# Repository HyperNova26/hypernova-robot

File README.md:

<div align="center">
  
  <p><strong>HyperNova 로봇 프로젝트</strong></p>
</div>

## 프로젝트

HyperNova는 스스로 움직이는 로봇을 직접 설계해서 만드는 팀 프로젝트입니다!

## 다루는 영역

- 이동과 기체 제어
- 주변 인지와 위치 추정
- 자율 임무 수행과 상태 보고
- 시험, 관제, 시스템 레벨 통합

## 저장소 구조

| 경로 | 역할 |
| --- | --- |
| [`docs/`](./docs/) | 프로젝트 범위, 아키텍처, 개발·운용 지침, 결정 기록 |
| [`description/`](./description/) | URDF·Xacro, frame·joint와 실행에 필요한 mesh |
| [`firmware/`](./firmware/) | 보드별 펌웨어, 플래시 및 진단 도구 |
| [`ros_pkgs/`](./ros_pkgs/) | 기능별 ROS 2 package와 관제 애플리케이션 |
| [`sim_scenes/`](./sim_scenes/) | 시뮬레이션 환경과 검증 시나리오 |
| [`policies/`](./policies/) | 학습 기반 policy의 학습·평가·export 코드와 설정 |
| [`tools/`](./tools/) | 개발·검증·변환 도구 |

## 시작하기

1. [프로젝트 범위](./docs/project-scope.md) — 무엇이 정해졌고 무엇이 아직 비어 있는지
2. [`CONTRIBUTING.md`](./CONTRIBUTING.md) — Issue에서 시작해 branch, Pull Request로 가는 흐름
3. [저장소 정책](./docs/development/repository-policy.md) — 큰 파일이나 센서 데이터를 올리기 전에
4. [안전 지침](./docs/operations/safety.md) — 실물에 전원을 넣기 전에

## 문서

- [문서 색인](./docs/README.md)
- [시뮬레이터 장면 변환 안내](./sim_scenes/README.md) — 전체 점군 변환과 미완성 segmentation의 현재 범위
- [ADR-0001: 단일 저장소로 시작](./docs/decisions/0001-monorepo-first.md)

2026-11-26 기준, `tools/`와 `tests/`의 코드는 처음 저장소에 들어온 날짜를 붙인 `MMDD_이름`으로 부릅니다. 맵 도구 목록과 PAIR360 지도 v1·v2·v3의 대응은 [도구 안내](./tools/README.md)에 있습니다.

## 라이선스

산출물 종류에 따라 라이선스가 다릅니다.

- 소프트웨어·펌웨어·시뮬레이션·학습·도구: Apache-2.0
- 기구·전자 설계와 그 파생 형상·제조 산출물: CERN-OHL-S-2.0
- 문서: CC BY 4.0
- HYPERNOVA 이름·로고·배너: 라이선스 대상 아님

적용 범위와 원문은 [`LICENSE.md`](./LICENSE.md)에 있습니다.

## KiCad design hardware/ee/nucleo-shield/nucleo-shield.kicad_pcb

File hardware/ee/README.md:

<!-- SPDX-License-Identifier: CC-BY-4.0 -->

# HyperNova Nucleo 캐리어 P2.3

2026-11-28 시제품 발주 전 설계 검토본입니다. NUCLEO-G474RE가 다리별 RS-485 버스 4개로 모터 12대를 제어합니다. KiCad 10.0.6에서 [전용 라이브러리를 포함한 프로젝트](nucleo-shield/nucleo-shield.kicad_pro)를 엽니다.

J17에는 부하가 걸린 상태에서 5.15–5.25 V인 안정화 전원을 연결합니다. F1과 LTC4364-2 공통 보호단을 지나 두 갈래로 나뉩니다. 한쪽은 J24에서 6 V로 승압한 뒤 U6·U14를 통해 Nucleo CN7-6과 J14-6에 전원을 공급합니다. 다른 쪽은 8핀 J23의 TI 벅을 통해 J19–J22의 RS-485 모듈 네 개에 전용 3.3 V를 공급합니다. Nucleo와 모듈은 GND를 공유합니다. 양쪽 전원이 유효하고 펌웨어의 공통 허용 신호와 채널별 DE가 켜져야 송신할 수 있습니다. J7–J11의 센서 전원은 Nucleo 3.3 V입니다.

J14의 CAN FD 모듈을 통해 Jetson에 통신하고, 외장 션트와 J13의 INA228으로 얻은 측정값을 Jetson의 배터리 잔량 표시에 사용합니다. J15는 라이다 동기 입력이고 J16은 필수 경고음용 피에조입니다. 모터 전력·퓨즈·비상 차단은 외부 하네스에 두며, PA11의 J18은 기본 미실장입니다.

| 검토 자료 | 확인할 내용 |
| --- | --- |
| [전원 계산서와 시제품 시험표](nucleo-shield/power-validation.md) · [계산 재현 스크립트](nucleo-shield/check-power-margins.py) | CN7·원격 RS 전압 여유, 기동·저전압 감시, 핫플러그 보호 범위와 시험 조건 |
| [KiCad 및 제조 파일 검증](nucleo-shield/verification.md) | 검사 환경과 결과, 동박 사양, Gerber·드릴 검토본 |
| [캐리어 BOM](nucleo-shield/carrier-bom.csv) · [구매 BOM](nucleo-shield/modules-and-mates.csv) | 실장·DNP, 완성 모듈, 커넥터와 하네스 부품의 구매 조건 |
| [조립 안내](nucleo-shield/assembly.md) · [하네스 제작표](nucleo-shield/harnesses.md) | 조립면, 핀 순서, 선경·길이, 종단·센스선 보호 |

발주 결정은 설계팀 검토 후 진행합니다. 시제품 전원과 통신의 실측 결과를 양산 판단에 사용합니다. 전자 설계에는 CERN-OHL-S-2.0, 문서에는 CC BY 4.0을 적용합니다. [저장소 라이선스](../../LICENSE.md)

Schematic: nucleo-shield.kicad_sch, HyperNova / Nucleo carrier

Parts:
C1: 4.7u; C_Disc_D5.0mm_W2.5mm_P2.50mm
C2, C5, C6, C7, C8, C15, C16, C17, C18, C19, C21: 100n; C_Disc_D5.0mm_W2.5mm_P2.50mm
C3, C14, C20: 22u / 25V X7R; C_Rect_L7.5mm_W6.5mm_P5.00mm
C4: 100n; C_Disc_D5.0mm_W2.5mm_P2.50mm; not fitted
C9: 22u / 50V NP; C_Radial_D10.0mm_H12.5mm_P5.00mm
C10: 10n; C_Disc_D5.0mm_W2.5mm_P2.50mm
C11: 12n C0G; C_Disc_D5.0mm_W2.5mm_P2.50mm
C12, C13, C25: 100n / 50V; C_Disc_D5.0mm_W2.5mm_P2.50mm
C22: 68n 5% / 50V; C_Rect_L7.2mm_W3.5mm_P5.00mm
C23: 47n 5% / 50V; C_Rect_L7.2mm_W3.5mm_P5.00mm
C24: 680u / 25V low ESR; CP_Radial_D10.0mm_P5.00mm
C26: 10u / 25V X7R; C_Rect_L7.5mm_W6.5mm_P5.00mm
D1: CAN; LED_D3.0mm
D2: RUN; LED_D3.0mm
D3: FAULT; LED_D3.0mm
D4, D5: BAT43; D_DO-35_SOD27_P2.54mm_Vertical_CathodeUp
D6, D7, D8: BAT43; D_DO-35_SOD27_P2.54mm_Vertical_CathodeUp; not fitted
D9: P6KE30CA; D_DO-15_P10.16mm_Horizontal
D10: SB1100-T; D_DO-41_SOD81_P7.62mm_Horizontal
D11: LM4040AIZ-2.5; TO-92_Inline
D12: 1N4750A 27V; D_DO-41_SOD81_P7.62mm_Horizontal
D13: BAT85; D_DO-35_SOD27_P2.54mm_Vertical_CathodeUp
D14, D15: BZX55C12; D_DO-35_SOD27_P2.54mm_Vertical_CathodeUp
D16: 5KP6.5A; Littelfuse_5KP_P20mm
D17: LT1634CCZ-2.5; TO-92_Inline
F1: 0251002.MXL; R_Axial_DIN0207_L6.3mm_D2.5mm_P10.16mm_Horizontal
J1: CN7 / MORPHO; Morpho_Socket_2x19_P2.54mm_Top_Mating
J2: CN10 / MORPHO; Morpho_Socket_2x19_P2.54mm_Top_Mating
J3: LEG1 RS485; JST_XH_S3B-XH-A_1x03_P2.50mm_Horizontal
J4: LEG2 RS485; JST_XH_S3B-XH-A_1x03_P2.50mm_Horizontal
J5: LEG3 RS485; JST_XH_S3B-XH-A_1x03_P2.50mm_Horizontal
J6: LEG4 RS485; JST_XH_S3B-XH-A_1x03_P2.50mm_Horizontal
J7: TOF1; JST_PH_S5B-PH-K_1x05_P2.00mm_Horizontal
J8: TOF2; JST_PH_S5B-PH-K_1x05_P2.00mm_Horizontal
J9: TOF3; JST_PH_S5B-PH-K_1x05_P2.00mm_Horizontal
J10: TOF4; JST_PH_S5B-PH-K_1x05_P2.00mm_Horizontal
J11: BMI088; PinHeader_1x09_P2.54mm_Vertical
J13: INA228 LOGIC; JST_PH_B4B-PH-K_1x04_P2.00mm_Vertical
J14: CAN FD 3 CLICK; JST_XH_B6B-XH-A_1x06_P2.50mm_Vertical
J15: JST-GH SYNC; JST_GH_SM04B-GHS-TB_1x04-1MP_P1.25mm_Horizontal
J16: BUZZER 3V3; JST_PH_B2B-PH-K_1x02_P2.00mm_Vertical
J17: REGULATED 5V; JST_XH_B2B-XH-A_1x02_P2.50mm_Vertical
J18: DRY NC CONTACT; JST_PH_B3B-PH-K_1x03_P2.00mm_Vertical; not fitted
J19, J20, J21, J22: TI THVD1424EVM; JST_XH_B7B-XH-A_1x07_P2.50mm_Vertical
J23: TPSM365R6V3EVM; JST_XH_B8B-XH-A_1x08_P2.50mm_Vertical
J24: POLOLU U3V16F6 #4942; Pololu_4942_VerticalSocket
Q1, Q2: 2N3904; TO-92_Inline
Q3, Q4: IRLZ44NPBF; TO-220-3_Vertical
R1, R7, R8, R19, R66: 10k; R_Axial_DIN0207_L6.3mm_D2.5mm_P2.54mm_Vertical
R6: 4.7k; R_Axial_DIN0207_L6.3mm_D2.5mm_P2.54mm_Vertical
R9, R10, R11, R12: 4.7k; R_Axial_DIN0207_L6.3mm_D2.5mm_P2.54mm_Vertical; not fitted
R13: 1.5k; R_Axial_DIN0207_L6.3mm_D2.5mm_P2.54mm_Vertical
R14, R15, R16, R17, R18: 1k; R_Axial_DIN0207_L6.3mm_D2.5mm_P2.54mm_Vertical
R28: 1k; R_Axial_DIN0207_L6.3mm_D2.5mm_P2.54mm_Vertical; not fitted
R29: 10k; R_Axial_DIN0207_L6.3mm_D2.5mm_P2.54mm_Vertical; not fitted
R30, R31, R32, R33: 120R; R_Axial_DIN0207_L6.3mm_D2.5mm_P2.54mm_Vertical; not fitted
R35: 93.1k 0.1%; R_Axial_DIN0207_L6.3mm_D2.5mm_P2.54mm_Vertical
R36: 3.9k; R_Axial_DIN0207_L6.3mm_D2.5mm_P2.54mm_Vertical
R37: 1.82k 0.1%; R_Axial_DIN0207_L6.3mm_D2.5mm_P2.54mm_Vertical
R38: 976R 1%; R_Axial_DIN0207_L6.3mm_D2.5mm_P2.54mm_Vertical
R39: 100R; R_Axial_DIN0207_L6.3mm_D2.5mm_P2.54mm_Vertical
R40: 3.30k; R_Axial_DIN0207_L6.3mm_D2.5mm_P2.54mm_Vertical
R41, R42: 10.0k 0.1%; R_Axial_DIN0207_L6.3mm_D2.5mm_P2.54mm_Vertical
R43: 33.2k 0.1%; R_Axial_DIN0207_L6.3mm_D2.5mm_P2.54mm_Vertical
R44, R46, R62: 10k 0.1%; R_Axial_DIN0207_L6.3mm_D2.5mm_P2.54mm_Vertical
R45: 19.1k 0.1%; R_Axial_DIN0207_L6.3mm_D2.5mm_P2.54mm_Vertical
R47: 22k; R_Axial_DIN0207_L6.3mm_D2.5mm_P2.54mm_Vertical
R48: 15k; R_Axial_DIN0207_L6.3mm_D2.5mm_P2.54mm_Vertical
R49, R50, R51, R52, R53, R54, R55, R56: 390R; R_Axial_DIN0207_L6.3mm_D2.5mm_P2.54mm_Vertical; not fitted
R57: 59.7k 0.1%; R_Axial_DIN0207_L6.3mm_D2.5mm_P2.54mm_Vertical
R61: 51.1k 0.1%; R_Axial_DIN0207_L6.3mm_D2.5mm_P2.54mm_Vertical
R63: 576R 0.1%; R_Axial_DIN0207_L6.3mm_D2.5mm_P2.54mm_Vertical
R64: 2.49k 0.1%; R_Axial_DIN0207_L6.3mm_D2.5mm_P2.54mm_Vertical
R65: 1.50k 1%; R_Axial_DIN0207_L6.3mm_D2.5mm_P2.54mm_Vertical
R67: 180R; R_Axial_DIN0207_L6.3mm_D2.5mm_P2.54mm_Vertical
R68: 27m / 5W / 10%; KOA_BPR58_P9.0mm
R69, R71: 3.48k 0.1%; R_Axial_DIN0207_L6.3mm_D2.5mm_P2.54mm_Vertical
R70, R72: 1.00k 0.1%; R_Axial_DIN0207_L6.3mm_D2.5mm_P2.54mm_Vertical
R73: 10R; R_Axial_DIN0207_L6.3mm_D2.5mm_P2.54mm_Vertical
R74: 0.68R / 3W pulse; Vishay_AC03_P17.78mm
R75: 0.33R / 5W pulse; Vishay_AC05_P25.4mm
RN1, RN3: 4x 4.7k; R_Array_SIP5
RN2, RN4, RN5: 4x 10k; R_Array_SIP5
RN6, RN7: 4x 47k; R_Array_SIP5
TP1: E5V_PROTECTED; TestPoint_THTPad_D1.5mm_Drill0.7mm
TP2: +3V3; TestPoint_THTPad_D1.5mm_Drill0.7mm
TP3: GND; TestPoint_THTPad_D1.5mm_Drill0.7mm
U1: 74HC08; DIP-14_W7.62mm
U6: LT3086ET7#PBF; TO-220-7_P2.54x3.7mm_StaggerOdd_Lead3.8mm_Vertical
U7: LM393AP; DIP-8_W7.62mm
U9, U10, U11: SN74AHC126N; DIP-14_W7.62mm
U13: LTC2909-3.3 / PA0089; ProtoAdvantage_PA0089_DIP8
U14: TPS2553 / PA0085; ProtoAdvantage_PA0085_DIP6
U15: SN74HC14N; DIP-14_W7.62mm
U16: LTC4364-2 / PA0005; ProtoAdvantage_PA0005_DIP16

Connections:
/+3V3: C1.1, C2.1, C17.1, D4.1 (K), D6.1 (K), D7.1 (K), J1.16, J7.1, J8.1, J9.1, J10.1, J11.1, J13.1, J14.1, J16.1, R6.1, R7.1, R8.1, R9.1, R10.1, R11.1, R12.1, R13.1, R29.1, R61.1, RN2.1 (common), TP2.1 (1_1), U1.14 (VCC), U11.14 (VCC)
/+3V3_RS485: C5.1, C6.1, C7.1, C8.1, C15.1, C16.1, C18.1, C21.1, D17.2 (K), J19.1, J20.1, J21.1, J22.1, J23.5, R49.2, R51.2, R53.2, R55.2, R65.1, RN3.1 (common), RN5.1 (common), U9.14 (VCC), U10.14 (VCC), U13.6 (VCC), U13.8 (SEL), U15.14 (VCC)
/BOOST_6V: C13.1, C26.1, J24.3, U6.5 (IN)
/BUCK_EN: D13.2 (A), J23.2
/BUZZER_BASE: Q1.2 (B), R18.2, R19.1
/BUZZER_PWM: J2.24, R18.1
/BUZZER_SINK: D6.2 (A), J16.2, Q1.3 (C)
/CAN_RX: J2.16, J14.4
/CAN_STB: J2.26, J14.5, R6.2
/CAN_TX: J2.30, J14.3
/E5V_ILIM: R57.1, U14.5 (ILIM)
/E5V_PROTECTED: C20.1, J1.6, J14.6, TP1.1 (1_1), U14.6 (OUT)
/E5V_REG: C3.1, C10.1, C14.1, C19.1, R35.1, R36.1, U6.3 (OUT), U14.1 (IN), U14.3 (EN)
/ESTOP_AUX_RAW: J18.1, R28.2
/ESTOP_STATUS: C4.1, D7.2 (A), D8.1 (K), J2.14, R28.1, R29.2
/EXT_5V_FUSED: C9.1, C25.1, D9.1 (A1), D10.2 (A), F1.1, R71.1, R75.1, U16.8 (VCC)
/EXT_5V_IN: F1.2, J17.1
/GND: C1.2, C2.2, C3.2, C4.2, C5.2, C6.2, C7.2, C8.2, C9.2, C11.2, C12.2, C13.2, C14.2, C15.2, C16.2, C17.2, C18.2, C19.2, C20.2, C21.2, C22.2, C23.2, C24.2, C25.2, C26.2, D1.1 (K), D2.1 (K), D3.1 (K), D5.2 (A), D8.2 (A), D9.2 (A2), D11.3 (A), D12.2 (A), D16.2 (A), J1.8, J1.19, J1.20, J1.22, J2.9, J2.20, J3.3, J4.3, J5.3, J6.3, J7.2, J8.2, J9.2, J10.2, J11.2, J13.2, J14.2, J15.2, J17.2, J18.3, J19.2, J20.2, J21.2, J22.2, J23.4, J23.6, J24.2, Q1.1 (E), R1.2, R19.2, R36.2, R37.2, R42.2, R44.2, R46.2, R48.2, R50.1, R52.1, R54.1, R56.1, R57.2, R62.2, R64.2, R66.2, R70.2, R72.2, RN1.1 (common), RN4.1 (common), RN6.1 (common), RN7.1 (common), TP3.1 (1_1), U1.7 (GND), U6.4 (GND), U7.4 (V-), U9.7 (GND), U10.7 (GND), U11.7 (GND), U13.4 (GND), U13.7 (TMR), U14.2 (GND), U15.5 (3A), U15.7 (GND), U15.9 (4A), U15.11 (5A), U15.13 (6A), U16.12 (GND)
/IMU_CSB1: J1.32, J11.6, R7.2
/IMU_CSB2: J1.34, J11.7, R8.2
/IMU_INT1: J1.35, J11.8
/IMU_INT3: J1.37, J11.9
/IMU_MISO: J2.13, J11.5
/IMU_MOSI: J2.15, J11.4
/IMU_SCK: J2.11, J11.3
/J17_AUX: C12.1, D12.1 (K), Q2.3 (C), R39.1, R40.1, R43.1, R45.1, U7.8 (V+)
/J17_COMP: C11.1, R38.2
/J17_DAMPED: Q3.2 (D), R75.2
/J17_DIODE: D10.1 (K), R39.2
/J17_GATE: D13.1 (K), Q2.2 (B), R47.2, U7.1, U7.7, U16.10 (UV)
/J17_HALF: R41.2, R42.1, U7.3 (+), U7.6 (-)
/J17_IMON: R37.1, R38.1, U6.1 (ILIM)
/J17_ISENSE: Q4.2 (D), R68.1, U16.2 (SENSE)
/J17_OV: R43.2, R44.1, U7.2 (-)
/J17_PROTECTED: C24.1, D16.1 (K), J24.1, R68.2, R69.1, R74.1, U16.1 (OUT)
/J17_REF: D11.2 (K), R40.2, R41.1, R47.1
/J17_SET: C10.2, R35.2, U6.2 (SET)
/J17_SHDN: Q2.1 (E), R48.1, U6.6 (SHDN)
/J17_UV: R45.2, R46.1, U7.5 (+)
/LED_CAN: J1.38, R15.1
/LED_FAULT: J2.33, R17.1
/LED_RUN: J1.36, R16.1
/LEG1_A: J3.1, J19.6, R30.2, R49.1
/LEG1_B: J3.2, J19.7, R30.1, R50.2
/LEG1_DE: J1.17, RN1.2 (R1), U1.1 (A)
/LEG1_DI: J19.4, RN5.2 (R1), U9.3 (1Y)
/LEG1_DRIVE: RN7.2 (R1), U1.3 (Y), U10.2 (1A)
/LEG1_RO: J19.3, RN3.2 (R1), U11.2 (1A)
/LEG1_RSE: J19.5, RN4.2 (R1), U10.3 (1Y)
/LEG1_RX: J1.2, RN2.2 (R1), U11.3 (1Y)
/LEG1_TX: J1.1, RN6.2 (R1), U9.2 (1A)
/LEG2_A: J4.1, J20.6, R31.2, R51.1
/LEG2_B: J4.2, J20.7, R31.1, R52.2
/LEG2_DE: J2.12, RN1.3 (R2), U1.4 (A)
/LEG2_DI: J20.4, RN5.3 (R2), U9.6 (2Y)
/LEG2_DRIVE: RN7.3 (R2), U1.6 (Y), U10.5 (2A)
/LEG2_RO: J20.3, RN3.3 (R2), U11.5 (2A)
/LEG2_RSE: J20.5, RN4.3 (R2), U10.6 (2Y)
/LEG2_RX: J2.6, RN2.3 (R2), U11.6 (2Y)
/LEG2_TX: J2.34, RN6.3 (R2), U9.5 (2A)
/LEG3_A: J5.1, J21.6, R32.2, R53.1
/LEG3_B: J5.2, J21.7, R32.1, R54.2
/LEG3_DE: J2.28, RN1.4 (R3), U1.9 (A)
/LEG3_DI: J21.4, RN5.4 (R3), U9.8 (3Y)
/LEG3_DRIVE: RN7.4 (R3), U1.8 (Y), U10.9 (3A)
/LEG3_RO: J21.3, RN3.4 (R3), U11.9 (3A)
/LEG3_RSE: J21.5, RN4.4 (R3), U10.8 (3Y)
/LEG3_RX: J2.18, RN2.4 (R3), U11.8 (3Y)
/LEG3_TX: J2.25, RN6.4 (R3), U9.9 (3A)
/LEG4_A: J6.1, J22.6, R33.2, R55.1
/LEG4_B: J6.2, J22.7, R33.1, R56.2
/LEG4_DE: J2.27, RN1.5 (R4), U1.12 (A)
/LEG4_DI: J22.4, RN5.5 (R4), U9.11 (4Y)
/LEG4_DRIVE: RN7.5 (R4), U1.11 (Y), U10.12 (4A)
/LEG4_RO: J22.3, RN3.5 (R4), U11.12 (4A)
/LEG4_RSE: J22.5, RN4.5 (R4), U10.11 (4Y)
/LEG4_RX: J1.4, RN2.5 (R4), U11.11 (4Y)
/LEG4_TX: J1.3, RN6.5 (R4), U9.12 (4A)
/LIDAR_SYNC_IN: D4.2 (A), D5.1 (K), J1.28, R14.1
/LOCAL_SCL: J2.2, J13.3, R11.2
/LOCAL_SDA: J2.1, J13.4, R12.2
/NUC_SENSE: R61.2, R62.1, U13.1 (ADJ1)
/RS485_TX_EN: J2.22, R1.1, U1.2 (B), U1.5 (B), U1.10 (B), U1.13 (B)
/RS_BUCK_VIN: J23.3, R74.2
/RS_EN_SRC: R67.1, U15.4 (2Y)
/RS_LINK_ENABLE: R66.1, R67.2, U9.1 (1OE), U9.4 (2OE), U9.10 (3OE), U9.13 (4OE), U10.1 (1OE), U10.4 (2OE), U10.10 (3OE), U10.13 (4OE), U11.1 (1OE), U11.4 (2OE), U11.10 (3OE), U11.13 (4OE)
/RS_OFFSET_NODE: D17.1 (Test), D17.3 (A), R63.1
/RS_OK: J23.1, R65.2, U13.5 (~RST), U15.1 (1A)
/RS_OK_N: U15.2 (1Y), U15.3 (2A)
/RS_SENSE: R63.2, R64.1, U13.2 (ADJ2)
/SURGE_DGATE: D15.1 (K), Q4.1 (G), U16.4 (DGATE)
/SURGE_FB: R69.2, R70.1, U16.16 (FB)
/SURGE_HGATE: C22.1, R73.1, U16.6 (HGATE)
/SURGE_OV: R71.2, R72.1, U16.11 (OV)
/SURGE_Q3G: D14.1 (K), Q3.1 (G), R73.2
/SURGE_SOURCE: D14.2 (A), D15.2 (A), Q3.3 (S), Q4.3 (S), U16.5 (SOURCE)
/SURGE_TIMER: C23.1, U16.15 (TMR)
/SYNC_EX_OUT: J15.1, R13.2, R14.2
/TOF1_XSHUT: J2.4, J7.5
/TOF2_XSHUT: J2.19, J8.5
/TOF3_XSHUT: J1.21, J9.5
/TOF4_XSHUT: J2.5, J10.5
/TOF_SCL: J2.21, J7.3, J8.3, J9.3, J10.3, R9.2
/TOF_SDA: J2.23, J7.4, J8.4, J9.4, J10.4, R10.2
unnamed: D1.2 (A), R15.2
unnamed: D2.2 (A), R16.2
unnamed: D3.2 (A), R17.2

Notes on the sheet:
CN10-14 PA11 is reserved (E-stop option DNP). CN10-35/37 duplicate PC4/PC5.
J23.5 and J1.16 are separate outputs. Verify >=3.00 V at both VCC and VIO on each enabled THVD1424EVM.
E5V / FINAL PRECISION CURRENT LIMIT
INA228 IN- = shunt load-side Kelvin terminal
Use the fixed-3.3 V TI EVM. Remove the EN jumper. J23.2 drives its EN divider through D13.
R9-R12 DNP. Module pull-ups and cable limits are specified in the harness table.
Pin 1 = 3.3 V. RX pull-up is local to the Nucleo UART.
Display battery SOC on Jetson via USB VCP.
CAN pair exits at the selected module. Check both 120R end terminations.
R57: 25 ppm/K max. Direct-solder factory-assembled DIP adapter. Monitor CN7-6 with TP1.
Choose the external shunt and protection from measured load and regeneration.
Use a GH-4 harness. J15.3 / J15.4 are reserved.
RS-485 / SCHMITT ENABLE DRIVER
RS-485 / FIXED 3.3 V BUCK AND POWER-GOOD INTERLOCK
CN7-23 B1 and PA2/PA3 ST-LINK VCP stay on the Nucleo.
Battery power, shunt sense branch protection, and motor cutoff are in the external harness.
CN7-6 receives protected E5V. CN7-16 feeds the MCU-side logic and sensor rail.
UART RX PULL-UP / TRANSMIT HI-Z
Battery + > Main fuse > External Kelvin shunt > Load distribution
All loads branch downstream. The motor branch has a hardware emergency cutoff.
LOCAL I2C3 / CAN-FD
P2.3 protected supplies | Two-layer bare PCB | Factory-fitted modules
U7 watches the raw rail. Its window controls U16 and U6, and inhibits the RS conversion through D13.
Use supplier-built DIP adapters, keyed module harnesses and the populated piezo assembly.
STATUS / BUZZER
TP4 PGOOD and U13 form an open-drain inhibit on RS_OK. Use separate input/output returns through J23.4/.6.
TI THVD1424EVM: enable the local 120R termination. Fit one 120R at the far end; R30-R33 remain DNP.
EXTERNAL E-STOP AUX CONTACT / STATUS
HYPERNOVA / 12-MOTOR NUCLEO CARRIER
SUPERVISOR / BOTH 3.3 V RAILS REQUIRED
ToF / DEDICATED I2C2
R67 limits the edge current into twelve OE inputs.
PA11 HIGH means pressed, contact open, or disconnected. LOW requires a closed dry contact.
Two inversions produce a fast enable edge after the U13 timeout.
RN2 holds MCU RX high when U11 is disabled. Fit the additional 10k module-end RSE-to-GND on each harness.
INA228 VBUS = fused battery side. Sense leads go directly to the module.
J13 is the low-voltage I2C connection. Shunt baseline 0.2 mOhm, ±1%.
Internal timeout 150-260 ms. 0.5 V adjustable threshold. RS_OK is LOW on either rail fault.
Default address 0x29. Hold XSHUT low, then release each sensor before assigning 0x30-0x33.
Confirm protected pulse levels and polarity on PA0.

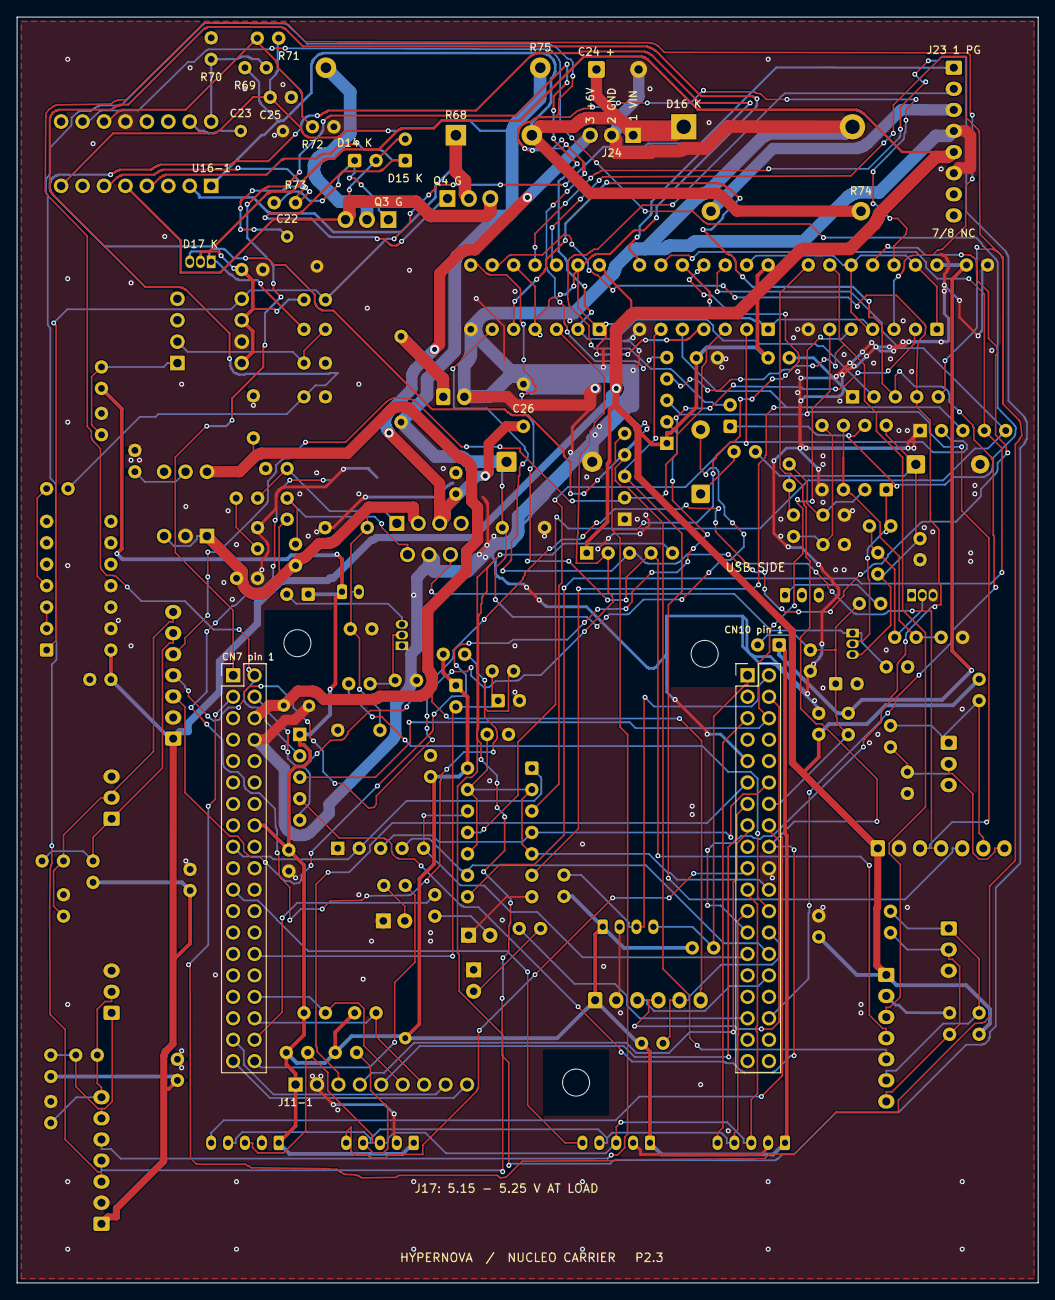
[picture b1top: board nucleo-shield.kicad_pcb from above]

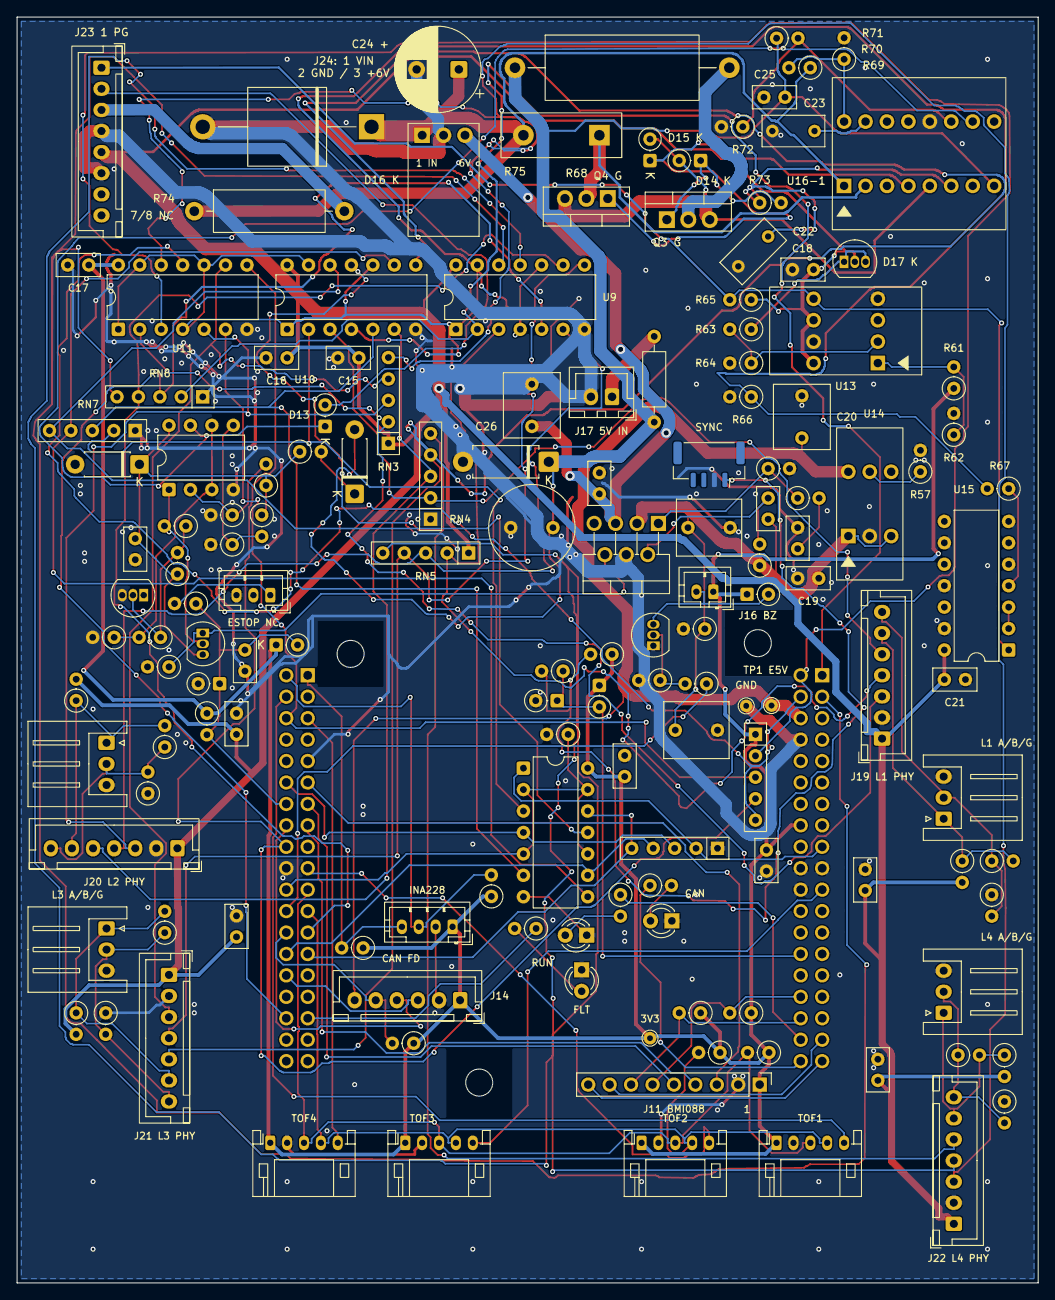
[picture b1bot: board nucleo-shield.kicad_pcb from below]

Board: 2 copper layers, 121.0 x 150.0 mm, 153 parts (148 on the bottom side), 107 nets.

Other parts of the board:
H1, H2, H3: MountingHole_3.2mm_M3_ISO14580

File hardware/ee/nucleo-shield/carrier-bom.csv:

"Reference","Value","Footprint","Quantity","DNP"
"C1","4.7u","Capacitor_THT:C_Disc_D5.0mm_W2.5mm_P2.50mm","1",""
"C2,C5-C8,C15-C19,C21","100n","Capacitor_THT:C_Disc_D5.0mm_W2.5mm_P2.50mm","11",""
"C3,C14,C20","22u / 25V X7R","Capacitor_THT:C_Rect_L7.5mm_W6.5mm_P5.00mm","3",""
"C4","100n","Capacitor_THT:C_Disc_D5.0mm_W2.5mm_P2.50mm","1","DNP"
"C9","22u / 50V NP","Capacitor_THT:C_Radial_D10.0mm_H12.5mm_P5.00mm","1",""
"C10","10n","Capacitor_THT:C_Disc_D5.0mm_W2.5mm_P2.50mm","1",""
"C11","12n C0G","Capacitor_THT:C_Disc_D5.0mm_W2.5mm_P2.50mm","1",""
"C12,C13,C25","100n / 50V","Capacitor_THT:C_Disc_D5.0mm_W2.5mm_P2.50mm","3",""
"C22","68n 5% / 50V","Capacitor_THT:C_Rect_L7.2mm_W3.5mm_P5.00mm","1",""
"C23","47n 5% / 50V","Capacitor_THT:C_Rect_L7.2mm_W3.5mm_P5.00mm","1",""
"C24","680u / 25V low ESR","Capacitor_THT:CP_Radial_D10.0mm_P5.00mm","1",""
"C26","10u / 25V X7R","Capacitor_THT:C_Rect_L7.5mm_W6.5mm_P5.00mm","1",""
"D1","CAN","LED_THT:LED_D3.0mm","1",""
"D2","RUN","LED_THT:LED_D3.0mm","1",""
"D3","FAULT","LED_THT:LED_D3.0mm","1",""
"D4,D5","BAT43","Diode_THT:D_DO-35_SOD27_P2.54mm_Vertical_CathodeUp","2",""
"D6-D8","BAT43","Diode_THT:D_DO-35_SOD27_P2.54mm_Vertical_CathodeUp","3","DNP"
"D9","P6KE30CA","Diode_THT:D_DO-15_P10.16mm_Horizontal","1",""
"D10","SB1100-T","Diode_THT:D_DO-41_SOD81_P7.62mm_Horizontal","1",""
"D11","LM4040AIZ-2.5","Package_TO_SOT_THT:TO-92_Inline","1",""
"D12","1N4750A 27V","Diode_THT:D_DO-41_SOD81_P7.62mm_Horizontal","1",""
"D13","BAT85","Diode_THT:D_DO-35_SOD27_P2.54mm_Vertical_CathodeUp","1",""
"D14,D15","BZX55C12","Diode_THT:D_DO-35_SOD27_P2.54mm_Vertical_CathodeUp","2",""
"D16","5KP6.5A","HyperNova:Littelfuse_5KP_P20mm","1",""
"D17","LT1634CCZ-2.5","Package_TO_SOT_THT:TO-92_Inline","1",""
"F1","0251002.MXL","Resistor_THT:R_Axial_DIN0207_L6.3mm_D2.5mm_P10.16mm_Horizontal","1",""
"J1","CN7 / MORPHO","HyperNova:Morpho_Socket_2x19_P2.54mm_Top_Mating","1",""
"J2","CN10 / MORPHO","HyperNova:Morpho_Socket_2x19_P2.54mm_Top_Mating","1",""
"J3","LEG1 RS485","Connector_JST:JST_XH_S3B-XH-A_1x03_P2.50mm_Horizontal","1",""
"J4","LEG2 RS485","Connector_JST:JST_XH_S3B-XH-A_1x03_P2.50mm_Horizontal","1",""
"J5","LEG3 RS485","Connector_JST:JST_XH_S3B-XH-A_1x03_P2.50mm_Horizontal","1",""
"J6","LEG4 RS485","Connector_JST:JST_XH_S3B-XH-A_1x03_P2.50mm_Horizontal","1",""
"J7","TOF1","Connector_JST:JST_PH_S5B-PH-K_1x05_P2.00mm_Horizontal","1",""
"J8","TOF2","Connector_JST:JST_PH_S5B-PH-K_1x05_P2.00mm_Horizontal","1",""
"J9","TOF3","Connector_JST:JST_PH_S5B-PH-K_1x05_P2.00mm_Horizontal","1",""
"J10","TOF4","Connector_JST:JST_PH_S5B-PH-K_1x05_P2.00mm_Horizontal","1",""
"J11","BMI088","Connector_PinHeader_2.54mm:PinHeader_1x09_P2.54mm_Vertical","1",""
"J13","INA228 LOGIC","Connector_JST:JST_PH_B4B-PH-K_1x04_P2.00mm_Vertical","1",""
"J14","CAN FD 3 CLICK","Connector_JST:JST_XH_B6B-XH-A_1x06_P2.50mm_Vertical","1",""
"J15","JST-GH SYNC","Connector_JST:JST_GH_SM04B-GHS-TB_1x04-1MP_P1.25mm_Horizontal","1",""
"J16","BUZZER 3V3","Connector_JST:JST_PH_B2B-PH-K_1x02_P2.00mm_Vertical","1",""
"J17","REGULATED 5V","Connector_JST:JST_XH_B2B-XH-A_1x02_P2.50mm_Vertical","1",""
"J18","DRY NC CONTACT","Connector_JST:JST_PH_B3B-PH-K_1x03_P2.00mm_Vertical","1","DNP"
"J19-J22","TI THVD1424EVM","Connector_JST:JST_XH_B7B-XH-A_1x07_P2.50mm_Vertical","4",""
"J23","TPSM365R6V3EVM","Connector_JST:JST_XH_B8B-XH-A_1x08_P2.50mm_Vertical","1",""
"J24","POLOLU U3V16F6 #4942","HyperNova:Pololu_4942_VerticalSocket","1",""
"Q1,Q2","2N3904","Package_TO_SOT_THT:TO-92_Inline","2",""
"Q3,Q4","IRLZ44NPBF","Package_TO_SOT_THT:TO-220-3_Vertical","2",""
"R1,R7,R8,R19,R66","10k","Resistor_THT:R_Axial_DIN0207_L6.3mm_D2.5mm_P2.54mm_Vertical","5",""
"R6","4.7k","Resistor_THT:R_Axial_DIN0207_L6.3mm_D2.5mm_P2.54mm_Vertical","1",""
"R9-R12","4.7k","Resistor_THT:R_Axial_DIN0207_L6.3mm_D2.5mm_P2.54mm_Vertical","4","DNP"
"R13","1.5k","Resistor_THT:R_Axial_DIN0207_L6.3mm_D2.5mm_P2.54mm_Vertical","1",""
"R14-R18","1k","Resistor_THT:R_Axial_DIN0207_L6.3mm_D2.5mm_P2.54mm_Vertical","5",""
"R28","1k","Resistor_THT:R_Axial_DIN0207_L6.3mm_D2.5mm_P2.54mm_Vertical","1","DNP"
"R29","10k","Resistor_THT:R_Axial_DIN0207_L6.3mm_D2.5mm_P2.54mm_Vertical","1","DNP"
"R30-R33","120R","Resistor_THT:R_Axial_DIN0207_L6.3mm_D2.5mm_P2.54mm_Vertical","4","DNP"
"R35","93.1k 0.1%","Resistor_THT:R_Axial_DIN0207_L6.3mm_D2.5mm_P2.54mm_Vertical","1",""
"R36","3.9k","Resistor_THT:R_Axial_DIN0207_L6.3mm_D2.5mm_P2.54mm_Vertical","1",""
"R37","1.82k 0.1%","Resistor_THT:R_Axial_DIN0207_L6.3mm_D2.5mm_P2.54mm_Vertical","1",""
"R38","976R 1%","Resistor_THT:R_Axial_DIN0207_L6.3mm_D2.5mm_P2.54mm_Vertical","1",""
"R39","100R","Resistor_THT:R_Axial_DIN0207_L6.3mm_D2.5mm_P2.54mm_Vertical","1",""
"R40","3.30k","Resistor_THT:R_Axial_DIN0207_L6.3mm_D2.5mm_P2.54mm_Vertical","1",""
"R41,R42","10.0k 0.1%","Resistor_THT:R_Axial_DIN0207_L6.3mm_D2.5mm_P2.54mm_Vertical","2",""
"R43","33.2k 0.1%","Resistor_THT:R_Axial_DIN0207_L6.3mm_D2.5mm_P2.54mm_Vertical","1",""
"R44,R46,R62","10k 0.1%","Resistor_THT:R_Axial_DIN0207_L6.3mm_D2.5mm_P2.54mm_Vertical","3",""
"R45","19.1k 0.1%","Resistor_THT:R_Axial_DIN0207_L6.3mm_D2.5mm_P2.54mm_Vertical","1",""
"R47","22k","Resistor_THT:R_Axial_DIN0207_L6.3mm_D2.5mm_P2.54mm_Vertical","1",""
"R48","15k","Resistor_THT:R_Axial_DIN0207_L6.3mm_D2.5mm_P2.54mm_Vertical","1",""
"R49-R56","390R","Resistor_THT:R_Axial_DIN0207_L6.3mm_D2.5mm_P2.54mm_Vertical","8","DNP"
"R57","59.7k 0.1%","Resistor_THT:R_Axial_DIN0207_L6.3mm_D2.5mm_P2.54mm_Vertical","1",""
"R61","51.1k 0.1%","Resistor_THT:R_Axial_DIN0207_L6.3mm_D2.5mm_P2.54mm_Vertical","1",""
"R63","576R 0.1%","Resistor_THT:R_Axial_DIN0207_L6.3mm_D2.5mm_P2.54mm_Vertical","1",""
"R64","2.49k 0.1%","Resistor_THT:R_Axial_DIN0207_L6.3mm_D2.5mm_P2.54mm_Vertical","1",""
"R65","1.50k 1%","Resistor_THT:R_Axial_DIN0207_L6.3mm_D2.5mm_P2.54mm_Vertical","1",""
"R67","180R","Resistor_THT:R_Axial_DIN0207_L6.3mm_D2.5mm_P2.54mm_Vertical","1",""
"R68","27m / 5W / 10%","HyperNova:KOA_BPR58_P9.0mm","1",""
"R69,R71","3.48k 0.1%","Resistor_THT:R_Axial_DIN0207_L6.3mm_D2.5mm_P2.54mm_Vertical","2",""
"R70,R72","1.00k 0.1%","Resistor_THT:R_Axial_DIN0207_L6.3mm_D2.5mm_P2.54mm_Vertical","2",""
"R73","10R","Resistor_THT:R_Axial_DIN0207_L6.3mm_D2.5mm_P2.54mm_Vertical","1",""
"R74","0.68R / 3W pulse","HyperNova:Vishay_AC03_P17.78mm","1",""
"R75","0.33R / 5W pulse","HyperNova:Vishay_AC05_P25.4mm","1",""
"RN1,RN3","4x 4.7k","Resistor_THT:R_Array_SIP5","2",""
"RN2,RN4,RN5","4x 10k","Resistor_THT:R_Array_SIP5","3",""
"RN6,RN7","4x 47k","Resistor_THT:R_Array_SIP5","2",""
"U1","74HC08","Package_DIP:DIP-14_W7.62mm","1",""
"U6","LT3086ET7#PBF","Package_TO_SOT_THT:TO-220-7_P2.54x3.7mm_StaggerOdd_Lead3.8mm_Vertical","1",""
"U7","LM393AP","Package_DIP:DIP-8_W7.62mm","1",""
"U9-U11","SN74AHC126N","Package_DIP:DIP-14_W7.62mm","3",""
"U13","LTC2909-3.3 / PA0089","HyperNova:ProtoAdvantage_PA0089_DIP8","1",""
"U14","TPS2553 / PA0085","HyperNova:ProtoAdvantage_PA0085_DIP6","1",""
"U15","SN74HC14N","Package_DIP:DIP-14_W7.62mm","1",""
"U16","LTC4364-2 / PA0005","HyperNova:ProtoAdvantage_PA0005_DIP16","1",""

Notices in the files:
hardware/ee/nucleo-shield/nucleo-shield.kicad_pcb:
SPDX-License-Identifier: CERN-OHL-S-2.0
parts and their libraries:
MB1367 under-board Morpho socket. Pin 2 right of pin 1 in module top view. CERN-OHL-S-2.0
License: SPDX-License-Identifier: CERN-OHL-S-2.0
